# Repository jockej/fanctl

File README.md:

# fanctl
A simple fan controller

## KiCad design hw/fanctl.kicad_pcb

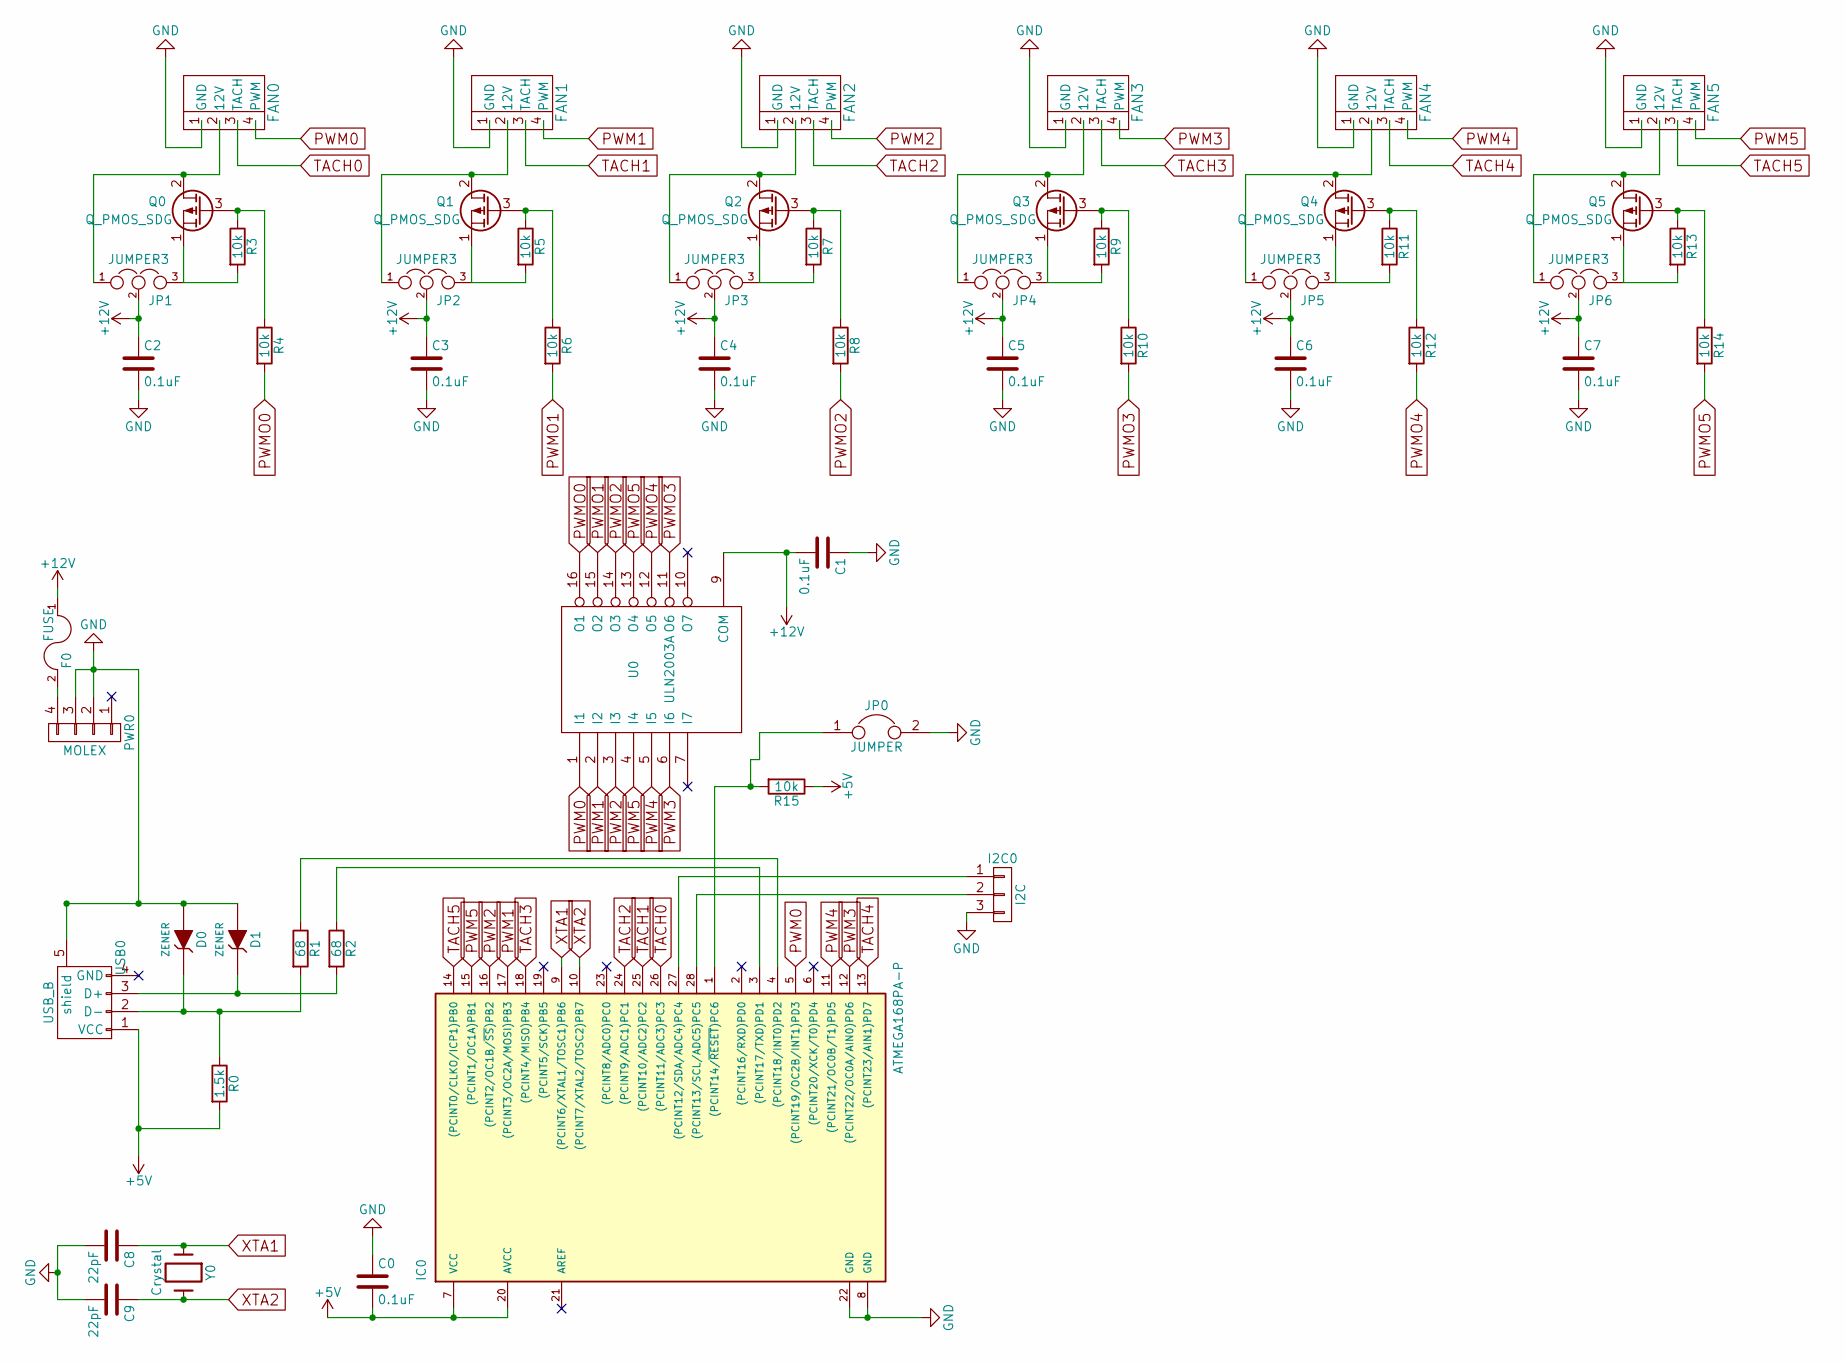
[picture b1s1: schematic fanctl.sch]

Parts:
C0, C1, C2, C3, C4, C5, C6, C7: 0.1uF; C_Disc_D3_P2.5
C8, C9: 22pF; C_Disc_D3_P2.5
D0, D1: ZENER; Diode_DO-35_SOD27_Horizontal_RM10; Voltage 3.6
F0: FUSE; Resistor_Horizontal_RM10mm
FAN0, FAN1, FAN2, FAN3, FAN4, FAN5: 4PIN_FAN; AB2_HDR_M04-1V_CPU_FAN
I2C0: I2C; Pin_Header_Straight_1x03
IC0: ATMEGA168PA-P; DIP-28_W7.62mm
JP0: JUMPER; Pin_Header_Straight_1x02
JP1, JP2, JP3, JP4, JP5, JP6: JUMPER3; Pin_Header_Straight_1x03
PWR0: MOLEX; AB2_ATX_PSU-4PIN-V
Q0, Q1, Q2, Q3, Q4: Q_PMOS_SDG; TO-220
Q5: Q_PMOS_SDG; TO-220; Part no FQP17P06
R0: 1.5k; Resistor_Horizontal_RM10mm
R1, R2: 68; Resistor_Horizontal_RM10mm
R3, R4, R5, R6, R7, R8, R9, R10, R11, R12, R13, R14, R15: 10k; Resistor_Horizontal_RM10mm
U0: ULN2003A; DIP-16_W7.62mm
USB0: USB_B
Y0: Crystal; Crystal_HC49-U_Vertical

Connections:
+5V: C0.2, IC0.7 (VCC), IC0.20 (AVCC), R0.2, R15.1, USB0.1 (VCC)
+12V: C1.2, C2.1, C3.1, C4.1, C5.1, C6.1, C7.1, F0.1, JP1.2, JP2.2, JP3.2, JP4.2, JP5.2, JP6.2, U0.9 (COM)
GND: C0.1, C1.1, C2.2, C3.2, C4.2, C5.2, C6.2, C7.2, C8.2, C9.2, D0.1 (A), D1.1 (A), FAN0.1 (GND), FAN1.1 (GND), FAN2.1 (GND), FAN3.1 (GND), FAN4.1 (GND), FAN5.1 (GND), I2C0.3, IC0.8 (GND), IC0.22 (GND), JP0.2, PWR0.2, PWR0.3, U0.8 (GND), USB0.5 (shield)
unnamed: D0.2 (K), R0.1, R1.2, USB0.2 (D-)
unnamed: D1.2 (K), R2.2, USB0.3 (D+)
unnamed: F0.2, PWR0.4
unnamed: FAN0.2 (12V), JP1.1, Q0.2 (D)
unnamed: FAN1.2 (12V), JP2.1, Q1.2 (D)
unnamed: FAN2.2 (12V), JP3.1, Q2.2 (D)
unnamed: FAN3.2 (12V), JP4.1, Q3.2 (D)
unnamed: FAN4.2 (12V), JP5.1, Q4.2 (D)
unnamed: FAN5.2 (12V), JP6.1, Q5.2 (D)
unnamed: I2C0.1, IC0.27 ((PCINT12/SDA/ADC4)PC4)
unnamed: I2C0.2, IC0.28 ((PCINT13/SCL/ADC5)PC5)
unnamed: IC0.1 ((PCINT14/~RESET~)PC6), JP0.1, R15.2
unnamed: IC0.3 ((PCINT17/TXD)PD1), R2.1
unnamed: IC0.4 ((PCINT18/INT0)PD2), R1.1
unnamed: JP1.3, Q0.1 (S), R3.2
unnamed: JP2.3, Q1.1 (S), R5.2
unnamed: JP3.3, Q2.1 (S), R7.2
unnamed: JP4.3, Q3.1 (S), R9.2
unnamed: JP5.3, Q4.1 (S), R11.2
unnamed: JP6.3, Q5.1 (S), R13.2
unnamed: Q0.3 (G), R3.1, R4.1
unnamed: Q1.3 (G), R5.1, R6.1
unnamed: Q2.3 (G), R7.1, R8.1
unnamed: Q3.3 (G), R9.1, R10.1
unnamed: Q4.3 (G), R11.1, R12.1
unnamed: Q5.3 (G), R13.1, R14.1
PWM0: FAN0.4 (PWM), IC0.5 ((PCINT19/OC2B/INT1)PD3), U0.1 (I1)
PWM1: FAN1.4 (PWM), IC0.17 ((PCINT3/OC2A/MOSI)PB3), U0.2 (I2)
PWM2: FAN2.4 (PWM), IC0.16 ((PCINT2/OC1B/~SS~)PB2), U0.3 (I3)
PWM3: FAN3.4 (PWM), IC0.12 ((PCINT22/OC0A/AIN0)PD6), U0.6 (I6)
PWM4: FAN4.4 (PWM), IC0.11 ((PCINT21/OC0B/T1)PD5), U0.5 (I5)
PWM5: FAN5.4 (PWM), IC0.15 ((PCINT1/OC1A)PB1), U0.4 (I4)
PWMO0: R4.2, U0.16 (O1)
PWMO1: R6.2, U0.15 (O2)
PWMO2: R8.2, U0.14 (O3)
PWMO3: R10.2, U0.11 (O6)
PWMO4: R12.2, U0.12 (O5)
PWMO5: R14.2, U0.13 (O4)
TACH0: FAN0.3 (TACH), IC0.26 ((PCINT11/ADC3)PC3)
TACH1: FAN1.3 (TACH), IC0.25 ((PCINT10/ADC2)PC2)
TACH2: FAN2.3 (TACH), IC0.24 ((PCINT9/ADC1)PC1)
TACH3: FAN3.3 (TACH), IC0.18 ((PCINT4/MISO)PB4)
TACH4: FAN4.3 (TACH), IC0.13 ((PCINT23/AIN1)PD7)
TACH5: FAN5.3 (TACH), IC0.14 ((PCINT0/CLKO/ICP1)PB0)
XTA1: C8.1, IC0.9 ((PCINT6/XTAL1/TOSC1)PB6), Y0.1
XTA2: C9.1, IC0.10 ((PCINT7/XTAL2/TOSC2)PB7), Y0.2

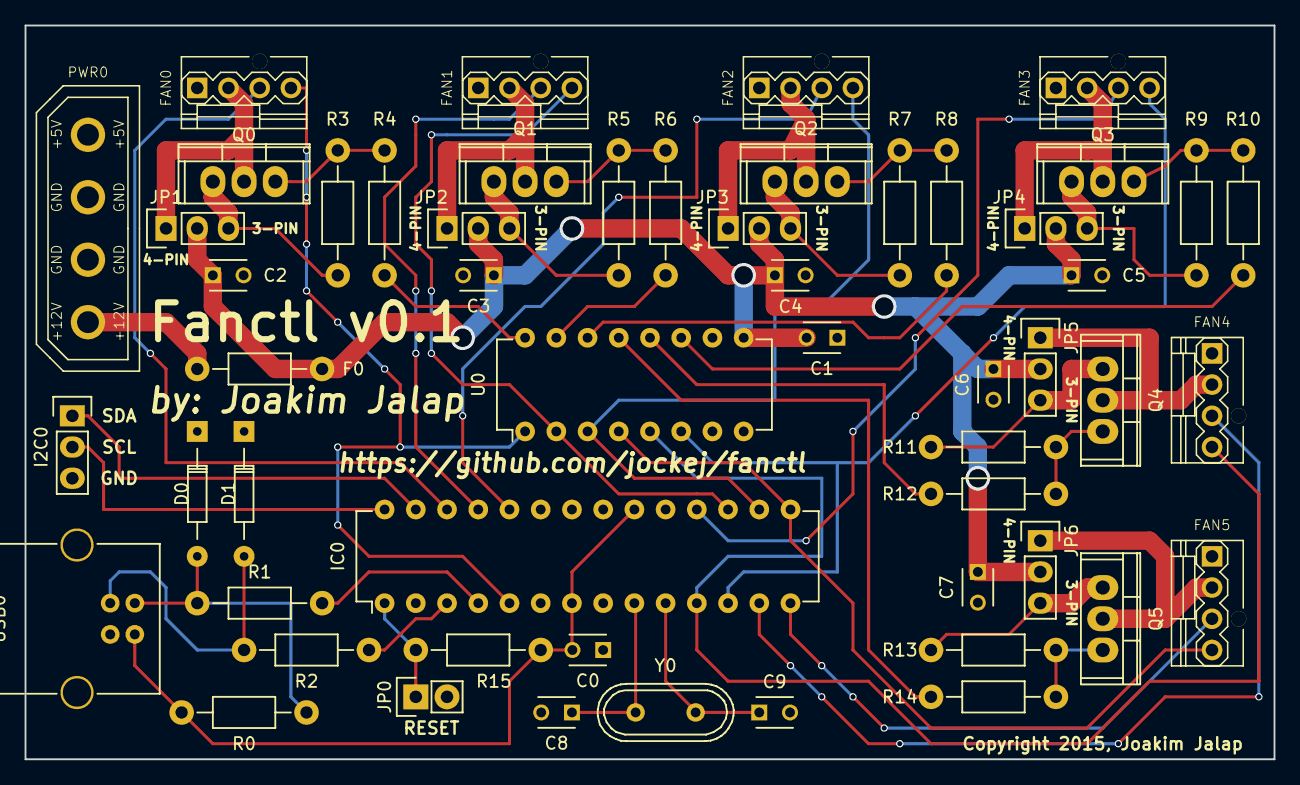
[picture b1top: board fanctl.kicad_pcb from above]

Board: 2 copper layers, 101.6 x 59.7 mm, 54 parts (0 on the bottom side), 49 nets.

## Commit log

2015-12-12 started on the schematics
2015-12-12 Some updates
2015-12-23 More changes
2015-12-24 Started PSB layout
2015-12-24 Some more files
2015-12-26 PCB pretty much done, I hope
2015-12-27 Some changes and gerber and drill files
2015-12-29 Some more changes

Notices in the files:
hw/fanctl.kicad_pcb:
Copyright 2015, Joakim Jalap
